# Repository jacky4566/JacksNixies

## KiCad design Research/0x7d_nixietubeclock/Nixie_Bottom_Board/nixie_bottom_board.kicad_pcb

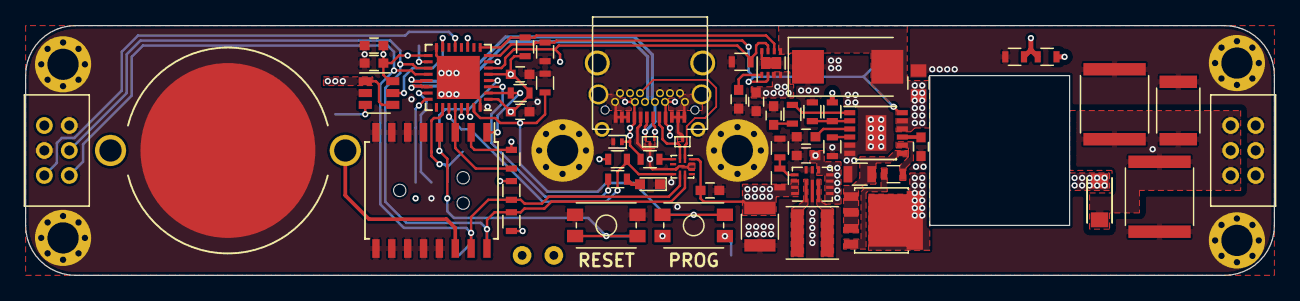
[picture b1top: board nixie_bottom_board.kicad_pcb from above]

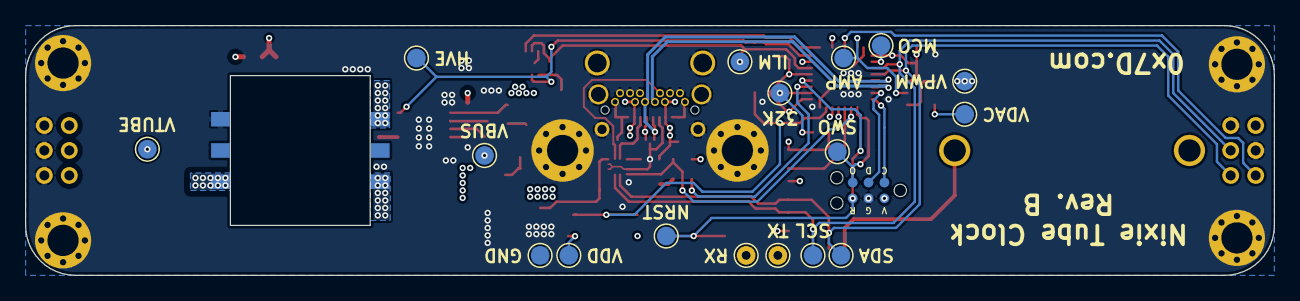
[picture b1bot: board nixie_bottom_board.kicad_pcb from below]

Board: 4 copper layers, 100.0 x 20.0 mm, 83 parts (18 on the bottom side), 49 nets.

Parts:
BT1: CR1620; CR1620_Holder_TH
C1: 330uF; CP_Tantalum_Case-X_EIA-7343-43_Reflow
C2, C12, C14, C15: 0.1uF; C_0603
C3: 10uF; C_0603
C4: C_IN; C_0805
C5: C_VC; C_0603
C6: C_SS; C_0603
C7: C_BP; C_0603
C8, C10: C_OUT; C_2220
C9: C_OUT; C_1812
C11: 220uF; C_1210
C13: 4.7uF; C_0603
C16: 1uF; C_0603
C17: SLEW; C_0603
D1: D_VBUS; X1SON
D2, D3: ESD122; DMX0003A
D4: D_RECT; SOD-123W
D5: LED; LED_0603
J1: USB_C_Receptacle; USB_C_Receptacle_Circular_Holes
J2: SWD; TC2030-MCP-NL
J3: Nixie_HV; Pin_Header_Harwin_2x03_Pitch2.00mm
J4: Nixie_CTRL; Pin_Header_Harwin_2x03_Pitch2.00mm
J5: MCO; TestPoint_Pad_D1.5mm
J6: ILM; TestPoint_Pad_D1.5mm
J7: HV_EN; TestPoint_Pad_D1.5mm
J8: HV_OUT; TestPoint_Pad_D1.5mm
J9: AMP_EN; TestPoint_Pad_D1.5mm
J10: 32kHz; TestPoint_Pad_D1.5mm
J11: SCL; TestPoint_Pad_D1.5mm
J12: SDA; TestPoint_Pad_D1.5mm
J13: DAC; TestPoint_Pad_D1.5mm
J14: VDD; TestPoint_Pad_D1.5mm
J15: VNIXIE; TestPoint_Pad_D1.5mm
J16: VBUS; TestPoint_Pad_D1.5mm
J17: SWO; TestPoint_Pad_D1.5mm
J18: NRST; TestPoint_Pad_D1.5mm
J19: TX; TestPoint_THTPad_D1.5mm_Drill0.7mm
J20: RX; TestPoint_THTPad_D1.5mm_Drill0.7mm
J21: GND; TestPoint_Pad_D1.5mm
L1: 1uH; Inductor_4.1x4.1mm
MH1, MH2, MH3, MH4, MH5, MH6: MountingHole_Pad; MountingHole_2.5mm_Pad_Via
Q1: Q_SWITCH; SOT-669_LFPAK
R1: 900k; R_0603
R2, R20: 1M; R_0603
R3, R12, R15, R19: 20k; R_0603
R4, R5, R13, R18: 10k; R_0603
R6: R_FREQ; R_0603
R7: R_VC; R_0603
R8: R_GATE; R_0603
R9: R_BIAS; R_0603
R10: R_FB; R_0603
R11: R_SENSE; R_0805
R14: 680; R_0603
R16: 560k; R_0603
R17: 180k; R_0603
R21: 15k; R_0603
SW1: NRST; EVQP2
SW2: DFU; EVQP2
T1: Wurth_Transformer_10.16x13.36mm; Wurth_WE-FB_10.18x13.36mm_Reverse
U1: TUSB322; X2QFN-12_1.6x1.6mm_Pitch0.4mm
U2: STM32L432K; QFN-32-1EP_5x5mm_Pitch0.5mm
U3: TPS63025X; VQFN-14_2.5x3mm_Pitch0.5mm
U4: DS3231; SOIC-16W_7.5x10.3mm_Pitch1.27mm
U5: AD8591; SOT-23-6
U6: LTC3759; MSOP-12-1EP_3x4mm_Pitch0.65mm
U7: TPS2595x0; WSON-8_1EP_2x2mm_Pitch0.5mm

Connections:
/32kHz: J10.1, R18.2, U2.2, U4.1
/AMP_EN: J9.1, U2.15, U5.5
/CC1: D2.2, J1.A5, U1.2
/CC2: D2.3, J1.B5, U1.1
/DAC: J13.1, U2.11, U5.3
/FAULT: R15.2, U2.9, U7.6
/GND: BT1.2, C1.1, C2.2, C3.2, C4.1, C5.2, C6.2, C7.2, C8.1, C9.1, C10.1, C11.1, C12.2, C13.2, C14.1, C15.1, C16.2, C17.2, D1.2, D2.1, D3.1, D5.1, J1.A1, J1.A2, J1.A3, J1.A8, J1.A10, J1.A11, J1.A12, J1.B1, J1.B2, J1.B3, J1.B8, J1.B10, J1.B11, J1.B12, J1.S1, J2.4, J3.2, J3.4, J3.6, J4.2, J4.3, J21.1, MH1.1, MH2.1, MH3.1, MH4.1, MH5.1, MH6.1, R2.2, R6.1, R9.1, R11.1, R12.2, R14.2, R17.1, R21.1, SW1.1, T1.1, U1.5, U1.10, U1.11, U2.16, U2.32, U2.33, U3.2, U3.9, U3.10, U4.5, U4.6, U4.7, U4.8, U4.9, U4.10, U4.11, U4.12, U4.13, U5.2, U6.5, U6.6, U6.13, U7.8, U7.9
/HV_EN: J7.1, R12.1, U2.8, U6.12, U7.2
/HV_IN: C1.2, C4.2, T1.6, U6.10, U6.11, U7.5
/HV_OUT: C8.2, C9.2, C10.2, D4.1, J3.1, J3.3, J3.5, J8.1, R10.1, R20.1
/ILM: J6.1, R14.1, U2.6, U7.7
/LED: R13.1, U2.3
/MCO: J5.1, U2.18
/NIXIE_EN: J4.5, U2.13
/NRST: J2.6, J18.1, SW1.2, U2.4, U4.4
/RTC: R19.1, U2.28, U4.3
/SCL: J4.4, J11.1, R5.1, U1.8, U2.19, U4.16
/SDA: J4.6, J12.1, R4.1, U1.7, U2.20, U4.15
/SWCLK: J2.1, U2.24
/SWDIO: J2.3, U2.23
/SWO: J2.5, J17.1, U2.26
/UART_RX: J20.1, U2.30
/UART_TX: J19.1, U2.29
/USB: R3.2, U1.6, U2.27
/USB_N: D3.3, J1.A7, J1.B7, U2.21
/USB_P: D3.2, J1.A6, J1.B6, U2.22
/VBUS: C2.1, C3.1, D1.1, J1.A4, J1.A9, J1.B4, J1.B9, J16.1, R1.1, U3.4, U3.5, U3.6, U3.7, U3.8, U7.3, U7.4
/VDD: C11.2, C12.1, C13.1, C14.2, C15.2, C16.1, J2.2, J14.1, R3.1, R4.2, R5.2, R15.1, R16.2, R18.1, R19.2, SW2.2, U1.12, U2.1, U2.5, U2.17, U3.12, U3.13, U3.14, U4.2, U5.6
/VNIXIE: J4.1, J15.1, U5.1, U5.4
unnamed: BT1.1, U4.14
unnamed: C5.1, R7.2
unnamed: C6.1, U6.3
unnamed: C7.1, U6.9
unnamed: C17.1, U7.1
unnamed: D4.2, T1.3
unnamed: D5.2, R13.2
unnamed: L1.1, U3.3
unnamed: L1.2, U3.1
unnamed: Q1.1, T1.4
unnamed: Q1.2, R8.1
unnamed: Q1.3, R11.2, U6.7
unnamed: R1.2, U1.3
unnamed: R2.1, SW2.1, U2.31
unnamed: R6.2, U6.4
unnamed: R7.1, U6.1
unnamed: R8.2, U6.8
unnamed: R9.2, R10.2, U6.2
unnamed: R16.1, R17.2, U3.11
unnamed: R20.2, R21.2, U2.7

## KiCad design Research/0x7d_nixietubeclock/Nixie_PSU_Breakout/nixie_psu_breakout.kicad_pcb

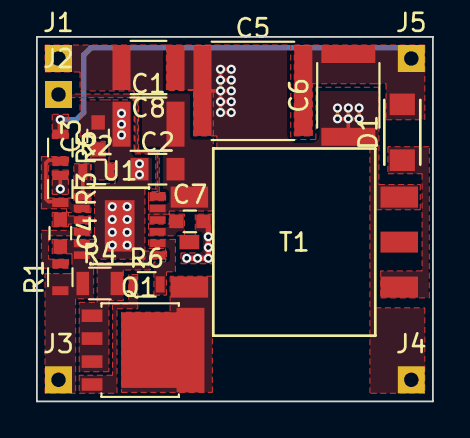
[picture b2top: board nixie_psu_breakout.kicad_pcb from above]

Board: 2 copper layers, 22.0 x 20.2 mm, 23 parts (0 on the bottom side), 15 nets.

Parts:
C1, C8: C_IN; C_1210
C2: C_IN; C_0805
C3: C_VC; C_0603
C4: C_SS; C_0603
C5: C_OUT; C_2220
C6: C_OUT; C_1812
C7: C_BP; C_0603
D1: D_RECT; SOD-123W
J1: VIN; Measurement_Point_Square-TH_Small
J2: EN; Measurement_Point_Square-TH_Small
J3, J4: GND; Measurement_Point_Square-TH_Small
J5: VOUT; Measurement_Point_Square-TH_Small
Q1: Q_SWITCH; SOT-669_LFPAK
R1: R_FREQ; R_0603
R2: R_VC; R_0603
R3: R_BIAS; R_0603
R4: R_SENSE; R_0805
R5: R_FB; R_0603
R6: R_GATE; R_0603
T1: Wurth_Transformer_10.16x13.36mm; Wurth_WE-FB_10.18x13.36mm
U1: LTC3759; MSOP-12-1EP_3x4mm_Pitch0.65mm

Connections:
GNDREF: C1.1, C2.1, C3.2, C4.2, C5.1, C6.1, C7.2, C8.1, J3.1, J4.1, R1.1, R3.1, R4.1, T1.1, U1.5, U1.6, U1.13
unnamed: C1.2, C2.2, C8.2, J1.1, T1.6, U1.10, U1.11
unnamed: C3.1, R2.2
unnamed: C4.1, U1.3
unnamed: C5.2, C6.2, D1.1, J5.1, R5.1
unnamed: C7.1, U1.9
unnamed: D1.2, T1.3
unnamed: J2.1, U1.12
unnamed: Q1.1, T1.4
unnamed: Q1.2, R6.1
unnamed: Q1.3, R4.2, U1.7
unnamed: R1.2, U1.4
unnamed: R2.1, U1.1
unnamed: R3.2, R5.2, U1.2
unnamed: R6.2, U1.8

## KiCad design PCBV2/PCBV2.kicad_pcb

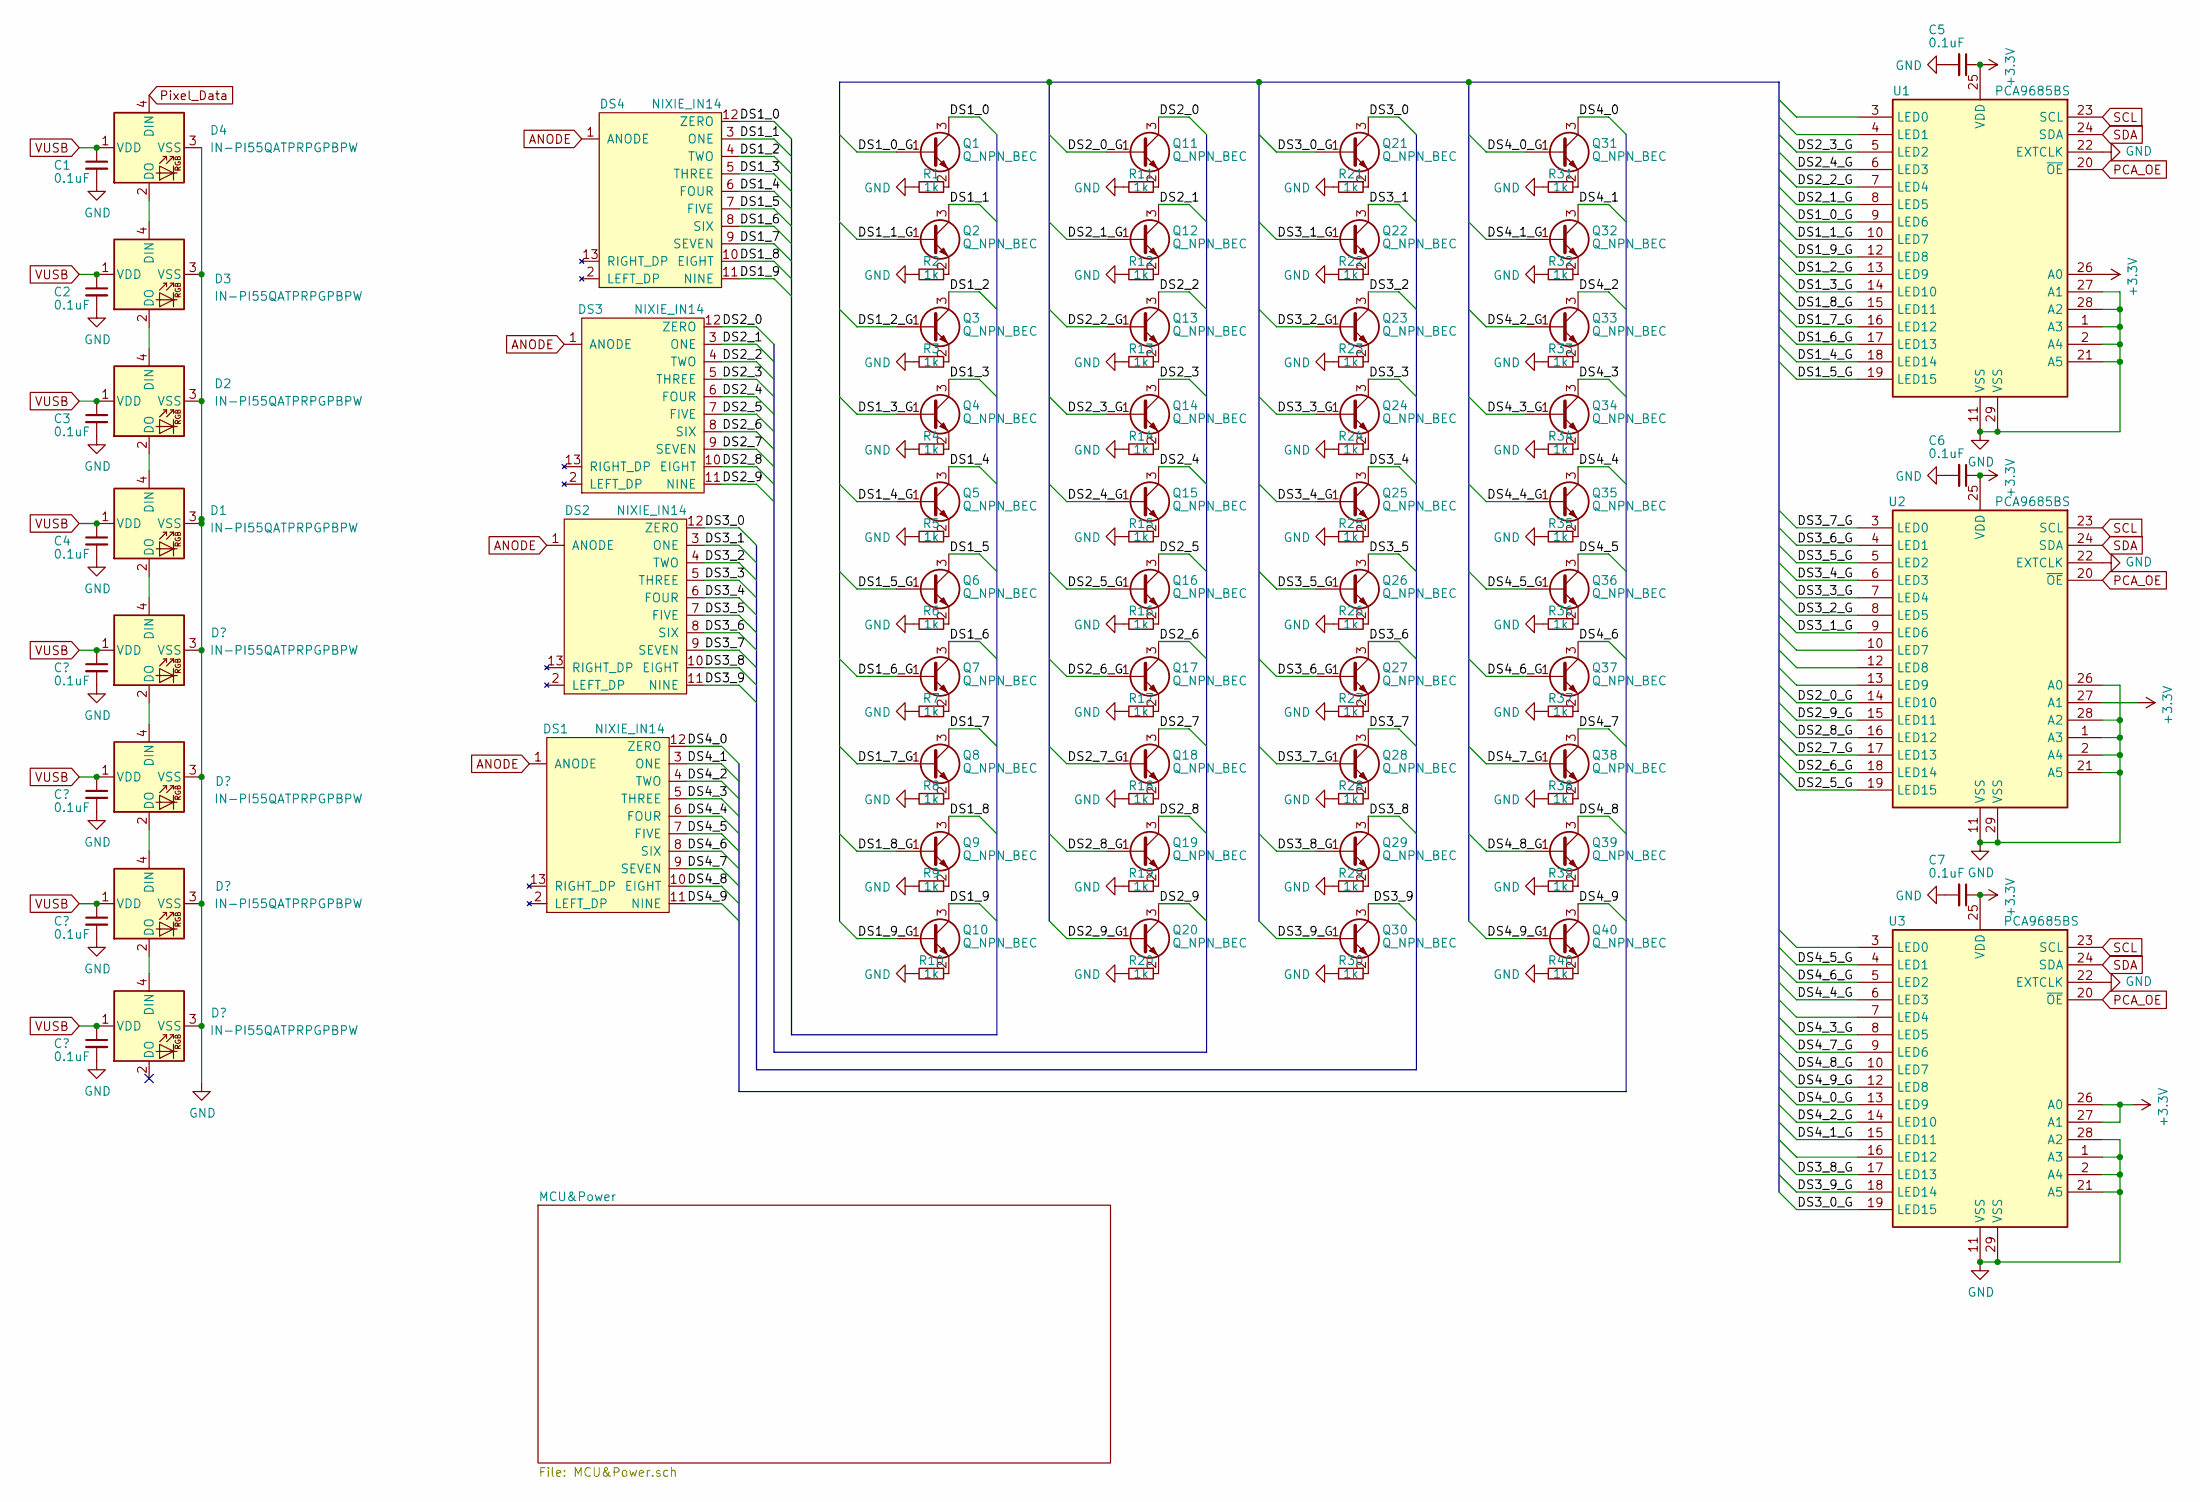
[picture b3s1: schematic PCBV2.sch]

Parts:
C1, C2, C3, C4, C5, C6, C7: 0.1uF; C_0603_1608Metric
D1, D2, D3, D4: IN-PI55QATPRPGPBPW; LED_Inolux_IN-PI554FCH_PLCC4_5.0x5.0mm_P3.2mm
DS1, DS2, DS3, DS4: NIXIE_IN14; Nixie_IN_14
Q1, Q2, Q3, Q4, Q5, Q6, Q7, Q8, Q9, Q10, Q11, Q12, Q13, Q14, Q15, Q16, Q17, Q18, Q19, Q20, Q21, Q22, Q23, Q24, Q25, Q26, Q27, Q28, Q29, Q30, Q31, Q32, Q33, Q34, Q35, Q36, Q37, Q38, Q39, Q40: Q_NPN_BEC; SOT-323; Manufacturer Part Number MSD42WT1G
R1, R2, R3, R4, R5, R6, R7, R8, R9, R10, R11, R12, R13, R14, R15, R16, R17, R18, R19, R20, R21, R22, R23, R24, R25, R26, R27, R28, R29, R30, R31, R32, R33, R34, R35, R36, R37, R38, R39, R40: 1k; R_0603_1608Metric
U1, U2, U3: PCA9685BS; QFN-28-1EP_6x6mm_P0.65mm_EP4.25x4.25mm_ThermalVias

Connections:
+3V3: C5.1, C6.1, C7.1, U1.25 (VDD), U1.26 (A0), U2.25 (VDD), U2.27 (A1), U3.25 (VDD), U3.26 (A0), U3.27 (A1); also elsewhere on the board
/DS1_0: DS4.12 (ZERO), Q1.3 (C)
/DS1_0_G: Q1.1 (B), U1.9 (LED6)
/DS1_1: DS4.3 (ONE), Q2.3 (C)
/DS1_1_G: Q2.1 (B), U1.10 (LED7)
/DS1_2: DS4.4 (TWO), Q3.3 (C)
/DS1_2_G: Q3.1 (B), U1.13 (LED9)
/DS1_3: DS4.5 (THREE), Q4.3 (C)
/DS1_3_G: Q4.1 (B), U1.14 (LED10)
/DS1_4: DS4.6 (FOUR), Q5.3 (C)
/DS1_4_G: Q5.1 (B), U1.18 (LED14)
/DS1_5: DS4.7 (FIVE), Q6.3 (C)
/DS1_5_G: Q6.1 (B), U1.19 (LED15)
/DS1_6: DS4.8 (SIX), Q7.3 (C)
/DS1_6_G: Q7.1 (B), U1.17 (LED13)
/DS1_7: DS4.9 (SEVEN), Q8.3 (C)
/DS1_7_G: Q8.1 (B), U1.16 (LED12)
/DS1_8: DS4.10 (EIGHT), Q9.3 (C)
/DS1_8_G: Q9.1 (B), U1.15 (LED11)
/DS1_9: DS4.11 (NINE), Q10.3 (C)
/DS1_9_G: Q10.1 (B), U1.12 (LED8)
/DS2_0: DS3.12 (ZERO), Q11.3 (C)
/DS2_0_G: Q11.1 (B), U2.14 (LED10)
/DS2_1: DS3.3 (ONE), Q12.3 (C)
/DS2_1_G: Q12.1 (B), U1.8 (LED5)
/DS2_2: DS3.4 (TWO), Q13.3 (C)
/DS2_2_G: Q13.1 (B), U1.7 (LED4)
/DS2_3: DS3.5 (THREE), Q14.3 (C)
/DS2_3_G: Q14.1 (B), U1.5 (LED2)
/DS2_4: DS3.6 (FOUR), Q15.3 (C)
/DS2_4_G: Q15.1 (B), U1.6 (LED3)
/DS2_5: DS3.7 (FIVE), Q16.3 (C)
/DS2_5_G: Q16.1 (B), U2.19 (LED15)
/DS2_6: DS3.8 (SIX), Q17.3 (C)
/DS2_6_G: Q17.1 (B), U2.18 (LED14)
/DS2_7: DS3.9 (SEVEN), Q18.3 (C)
/DS2_7_G: Q18.1 (B), U2.17 (LED13)
/DS2_8: DS3.10 (EIGHT), Q19.3 (C)
/DS2_8_G: Q19.1 (B), U2.16 (LED12)
/DS2_9: DS3.11 (NINE), Q20.3 (C)
/DS2_9_G: Q20.1 (B), U2.15 (LED11)
/DS3_0: DS2.12 (ZERO), Q21.3 (C)
/DS3_0_G: Q21.1 (B), U3.19 (LED15)
/DS3_1: DS2.3 (ONE), Q22.3 (C)
/DS3_1_G: Q22.1 (B), U2.9 (LED6)
/DS3_2: DS2.4 (TWO), Q23.3 (C)
/DS3_2_G: Q23.1 (B), U2.8 (LED5)
/DS3_3: DS2.5 (THREE), Q24.3 (C)
/DS3_3_G: Q24.1 (B), U2.7 (LED4)
/DS3_4: DS2.6 (FOUR), Q25.3 (C)
/DS3_4_G: Q25.1 (B), U2.6 (LED3)
/DS3_5: DS2.7 (FIVE), Q26.3 (C)
/DS3_5_G: Q26.1 (B), U2.5 (LED2)
/DS3_6: DS2.8 (SIX), Q27.3 (C)
/DS3_6_G: Q27.1 (B), U2.4 (LED1)
/DS3_7: DS2.9 (SEVEN), Q28.3 (C)
/DS3_7_G: Q28.1 (B), U2.3 (LED0)
/DS3_8: DS2.10 (EIGHT), Q29.3 (C)
/DS3_8_G: Q29.1 (B), U3.17 (LED13)
/DS3_9: DS2.11 (NINE), Q30.3 (C)
/DS3_9_G: Q30.1 (B), U3.18 (LED14)
/DS4_0: DS1.12 (ZERO), Q31.3 (C)
/DS4_0_G: Q31.1 (B), U3.13 (LED9)
/DS4_1: DS1.3 (ONE), Q32.3 (C)
/DS4_1_G: Q32.1 (B), U3.15 (LED11)
/DS4_2: DS1.4 (TWO), Q33.3 (C)
/DS4_2_G: Q33.1 (B), U3.14 (LED10)
/DS4_3: DS1.5 (THREE), Q34.3 (C)
/DS4_3_G: Q34.1 (B), U3.8 (LED5)
/DS4_4: DS1.6 (FOUR), Q35.3 (C)
/DS4_4_G: Q35.1 (B), U3.6 (LED3)
/DS4_5: DS1.7 (FIVE), Q36.3 (C)
/DS4_5_G: Q36.1 (B), U3.4 (LED1)
/DS4_6: DS1.8 (SIX), Q37.3 (C)
/DS4_6_G: Q37.1 (B), U3.5 (LED2)
/DS4_7: DS1.9 (SEVEN), Q38.3 (C)
/DS4_7_G: Q38.1 (B), U3.9 (LED6)
/DS4_8: DS1.10 (EIGHT), Q39.3 (C)
/DS4_8_G: Q39.1 (B), U3.10 (LED7)
/DS4_9: DS1.11 (NINE), Q40.3 (C)
/DS4_9_G: Q40.1 (B), U3.12 (LED8)
ANODE: DS1.1 (ANODE), DS2.1 (ANODE), DS3.1 (ANODE), DS4.1 (ANODE); also elsewhere on the board
GND: C1.2, C2.2, C3.2, C4.2, C5.2, C6.2, C7.2, D1.3 (VSS), D2.3 (VSS), D3.3 (VSS), D4.3 (VSS), R1.2, R2.2, R3.2, R4.2, R5.2, R6.2, R7.2, R8.2, R9.2, R10.2, R11.2, R12.2, R13.2, R14.2, R15.2, R16.2, R17.2, R18.2, R19.2, R20.2, R21.2, R22.2, R23.2, R24.2, R25.2, R26.2, R27.2, R28.2, R29.2, R30.2, R31.2, R32.2, R33.2, R34.2, R35.2, R36.2, R37.2, R38.2, R39.2, R40.2, U1.1 (A3), U1.2 (A4), U1.11 (VSS), U1.21 (A5), U1.22 (EXTCLK), U1.27 (A1), U1.28 (A2), U1.29 (VSS), U2.1 (A3), U2.2 (A4), U2.11 (VSS), U2.21 (A5), U2.22 (EXTCLK), U2.26 (A0), U2.28 (A2), U2.29 (VSS), U3.1 (A3), U3.2 (A4), U3.11 (VSS), U3.21 (A5), U3.22 (EXTCLK), U3.28 (A2), U3.29 (VSS); also elsewhere on the board
unnamed: D1.4 (DIN), D2.2 (DO)
unnamed: D2.4 (DIN), D3.2 (DO)
unnamed: D3.4 (DIN), D4.2 (DO)
unnamed: Q1.2 (E), R1.1
unnamed: Q2.2 (E), R2.1
unnamed: Q3.2 (E), R3.1
unnamed: Q4.2 (E), R4.1
unnamed: Q5.2 (E), R5.1
unnamed: Q6.2 (E), R6.1
unnamed: Q7.2 (E), R7.1
unnamed: Q8.2 (E), R8.1
unnamed: Q9.2 (E), R9.1
unnamed: Q10.2 (E), R10.1
unnamed: Q11.2 (E), R11.1
unnamed: Q12.2 (E), R12.1
unnamed: Q13.2 (E), R13.1
unnamed: Q14.2 (E), R14.1
unnamed: Q15.2 (E), R15.1
unnamed: Q16.2 (E), R16.1
unnamed: Q17.2 (E), R17.1
unnamed: Q18.2 (E), R18.1
unnamed: Q19.2 (E), R19.1
unnamed: Q20.2 (E), R20.1
unnamed: Q21.2 (E), R21.1
unnamed: Q22.2 (E), R22.1
unnamed: Q23.2 (E), R23.1
unnamed: Q24.2 (E), R24.1
unnamed: Q25.2 (E), R25.1
unnamed: Q26.2 (E), R26.1
unnamed: Q27.2 (E), R27.1
unnamed: Q28.2 (E), R28.1
unnamed: Q29.2 (E), R29.1
unnamed: Q30.2 (E), R30.1
unnamed: Q31.2 (E), R31.1
unnamed: Q32.2 (E), R32.1
unnamed: Q33.2 (E), R33.1
unnamed: Q34.2 (E), R34.1
unnamed: Q35.2 (E), R35.1
unnamed: Q36.2 (E), R36.1
unnamed: Q37.2 (E), R37.1
unnamed: Q38.2 (E), R38.1
unnamed: Q39.2 (E), R39.1
unnamed: Q40.2 (E), R40.1
PCA_OE: U1.20 (~OE), U2.20 (~OE), U3.20 (~OE); also elsewhere on the board
Pixel_Data: D4.4 (DIN); also elsewhere on the board
SCL: U1.23 (SCL), U2.23 (SCL), U3.23 (SCL); also elsewhere on the board
SDA: U1.24 (SDA), U2.24 (SDA), U3.24 (SDA); also elsewhere on the board
VUSB: C1.1, C2.1, C3.1, C4.1, D1.1 (VDD), D2.1 (VDD), D3.1 (VDD), D4.1 (VDD); also elsewhere on the board

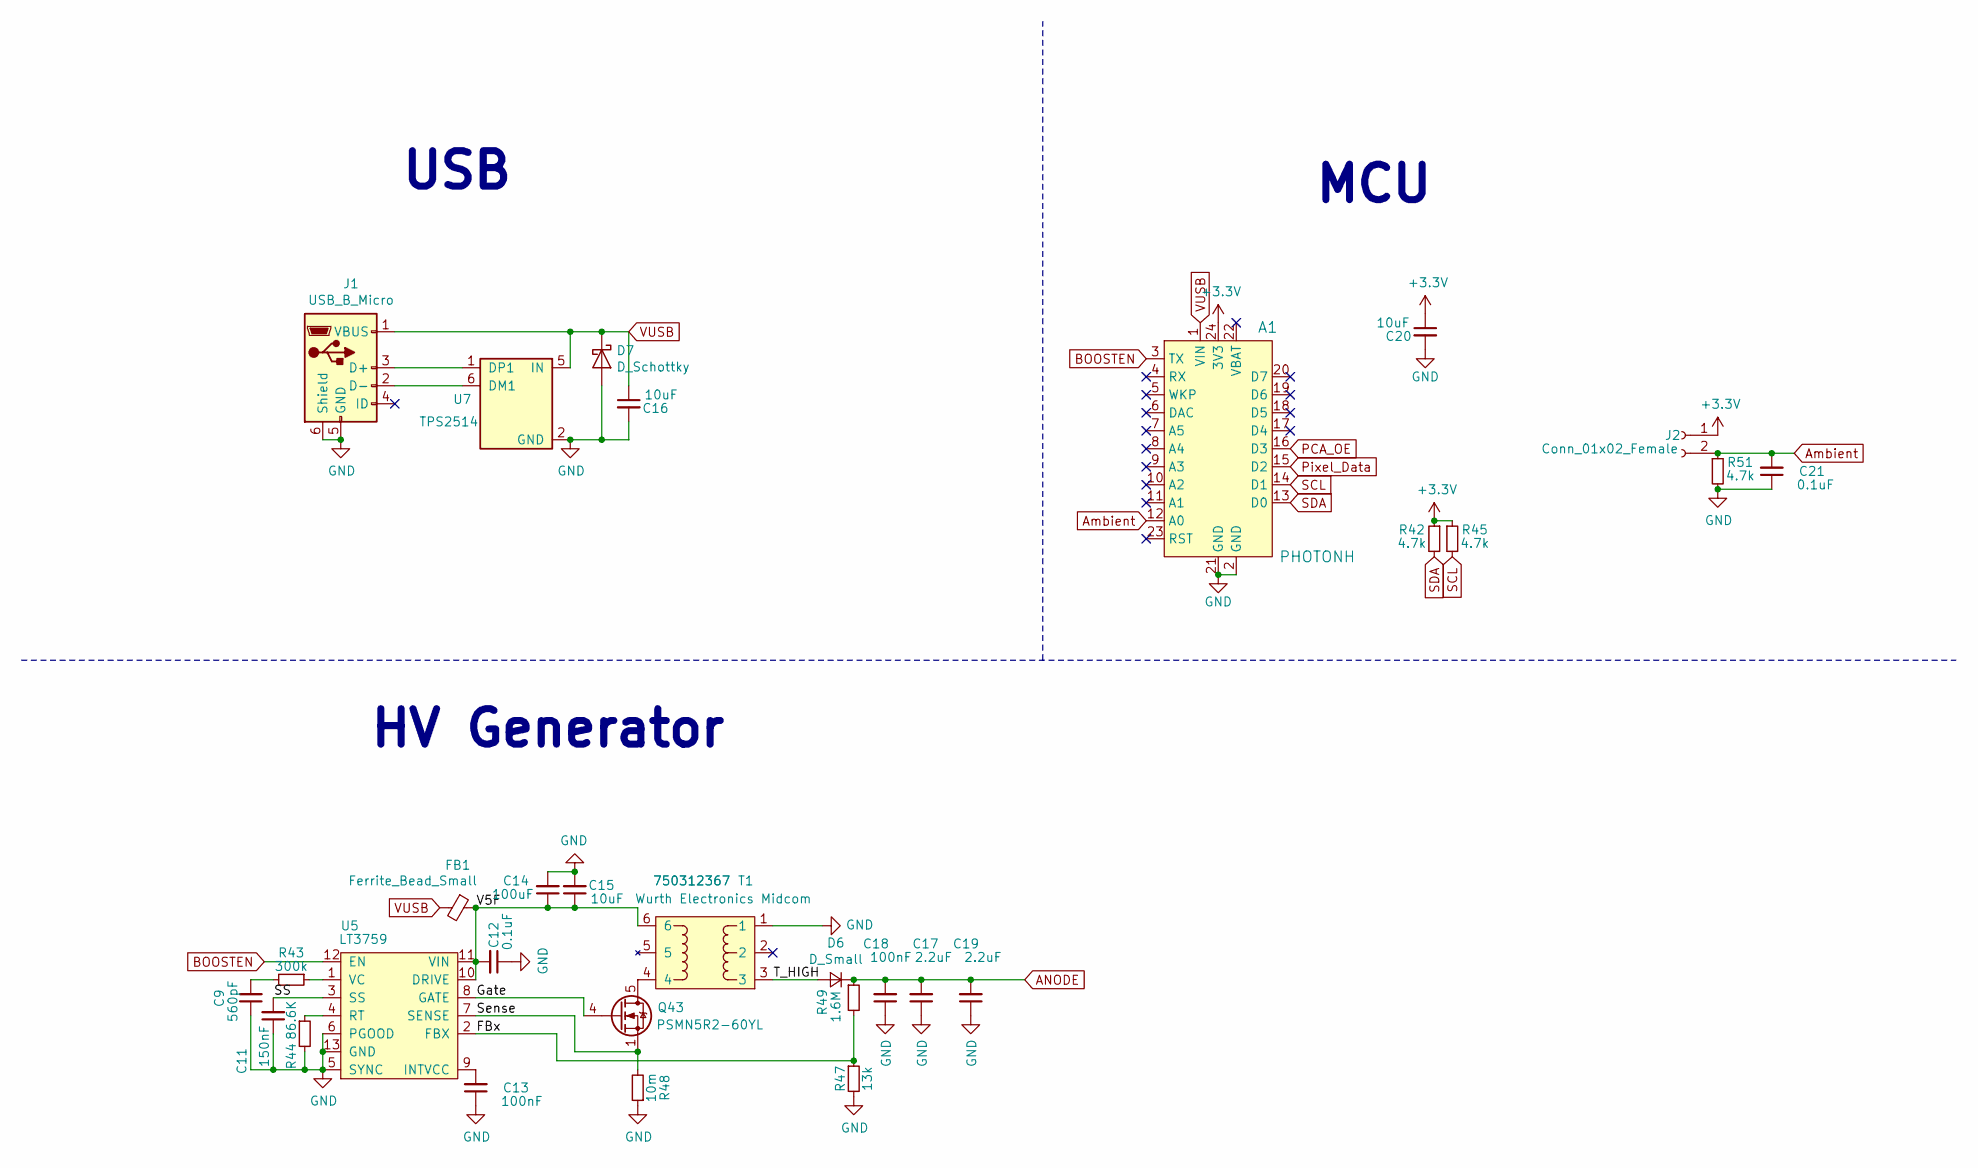
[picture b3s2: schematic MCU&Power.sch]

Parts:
A1: PHOTONH; Particle_Photon; MPN PHOTONH; Digi-Key_PN 1878-1000-ND
C9: 560pF; C_0603_1608Metric
C11: 150nF; C_0603_1608Metric
C12, C21: 0.1uF; C_0603_1608Metric
C13: 100nF; C_0603_1608Metric
C14: 100uF; C_1206_3216Metric
C15, C16, C20: 10uF; C_0805_2012Metric
C17, C19: 2.2uF; C_2220_5650Metric
C18: 100nF; C_1210_3225Metric
D6: D_Small; D_SOD-123; Part UF1GLWHRVGCT-ND
D7: D_Schottky; D_SOD-123
FB1: Ferrite_Bead_Small; R_0805_2012Metric
J1: USB_B_Micro; USB_Micro-B_GCT_USB3076-30-A
J2: Conn_01x02_Female; PinHeader_1x02_P2.54mm_Vertical
Q43: PSMN5R2-60YL; LFPAK56
R42, R45, R51: 4.7k; R_0603_1608Metric
R43: 300k; R_0603_1608Metric
R44: 86.6K; R_0603_1608Metric
R47: 13k; R_0603_1608Metric
R48: 10m; R_1206_3216Metric
R49: 1.6M; R_0603_1608Metric
T1: 750312367; Manufacturer Part Number 750312367
U5: LT3759; MSOP-12-1EP_3x4mm_P0.65mm_EP1.65x2.85mm_ThermalVias
U7: TPS2514; SOT-23-6

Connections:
+3V3: A1.24 (3V3), C20.1, J2.1, R42.1, R45.1; also elsewhere on the board
/MCU&Power/FBx: R47.1, R49.2, U5.2 (FBX)
/MCU&Power/Gate: Q43.4 (G), U5.8 (GATE)
/MCU&Power/SPI_CLK: A1.9 (A3); also elsewhere on the board
/MCU&Power/SPI_CS: A1.10 (A2); also elsewhere on the board
/MCU&Power/SPI_MISO: A1.8 (A4); also elsewhere on the board
/MCU&Power/SPI_MOSI: A1.7 (A5); also elsewhere on the board
/MCU&Power/SS: C11.2, U5.3 (SS)
/MCU&Power/Sense: Q43.1 (S), Q43.2 (S), Q43.3 (S), R48.2, U5.7 (SENSE)
/MCU&Power/T_HIGH: D6.2 (A), T1.3
/MCU&Power/V5F: C12.2, C14.1, C15.1, FB1.1, T1.6, U5.10 (DRIVE), U5.11 (VIN)
ANODE: C17.2, C18.2, C19.2, D6.1 (K), R49.1; also elsewhere on the board
Ambient: A1.12 (A0), C21.2, J2.2, R51.1
BOOSTEN: A1.3 (TX), U5.12 (EN)
GND: A1.2 (GND), A1.21 (GND), C9.1, C11.1, C12.1, C13.1, C14.2, C15.2, C16.2, C17.1, C18.1, C19.1, C20.2, C21.1, D7.2 (A), J1.5 (GND), J1.6 (Shield), R44.2, R47.2, R48.1, R51.2, T1.1, U5.5 (SYNC), U5.6 (PGOOD), U5.13 (GND), U7.2 (GND); also elsewhere on the board
MOTION: A1.17 (D4); also elsewhere on the board
unnamed: C9.2, R43.2
unnamed: C13.2, U5.9 (INTVCC)
unnamed: J1.2 (D-), U7.6 (DM1)
unnamed: J1.3 (D+), U7.1 (DP1)
unnamed: Q43.5 (D), T1.4
unnamed: R43.1, U5.1 (VC)
unnamed: R44.1, U5.4 (RT)
PCA_OE: A1.16 (D3); also elsewhere on the board
Pixel_Data: A1.15 (D2); also elsewhere on the board
SCL: A1.14 (D1), R45.2; also elsewhere on the board
SDA: A1.13 (D0), R42.2; also elsewhere on the board
SenseHigh: A1.20 (D7); also elsewhere on the board
VUSB: A1.1 (VIN), C16.1, D7.1 (K), FB1.2, J1.1 (VBUS), U7.5 (IN); also elsewhere on the board

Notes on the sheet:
USB
HV Generator
MCU

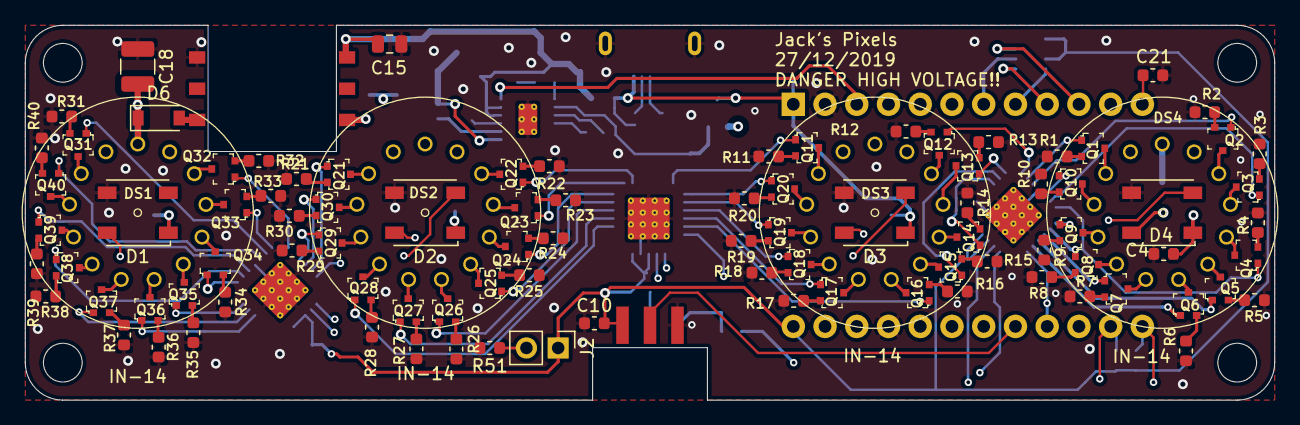
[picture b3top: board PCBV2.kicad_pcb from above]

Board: 4 copper layers, 100.0 x 30.0 mm, 135 parts (0 on the bottom side), 154 nets.

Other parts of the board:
C8, C10: 0.1uF; C_0603_1608Metric
R41, R50: 1M; R_0603_1608Metric
R46: 86.6k; R_0603_1608Metric
U6: BME680; Bosch_LGA-8_3x3mm_P0.8mm_ClockwisePinNumbering
U8: AM612; AM612_Horz

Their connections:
+3V3: C8.1, C10.2, R50.2, U6.6, U6.8, U8.4; also elsewhere on the board
/MCU&Power/SPI_CLK: U6.4; also elsewhere on the board
/MCU&Power/SPI_CS: U6.2; also elsewhere on the board
/MCU&Power/SPI_MISO: U6.5; also elsewhere on the board
/MCU&Power/SPI_MOSI: U6.3; also elsewhere on the board
GND: C8.2, C10.1, R46.2, U6.1, U6.7, U8.3, U8.6; also elsewhere on the board
MOTION: U8.5; also elsewhere on the board
unnamed: R41.2, R46.1, U8.1
unnamed: R50.1, U8.2
SenseHigh: R41.1; also elsewhere on the board

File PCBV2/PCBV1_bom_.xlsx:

Component | Description | Part | References | Value | Footprint | Quantity Per PCB | Digikey Part Num
1 | PHOTON WITH HEADERS | PHOTONH | A1 | PHOTONH | Particle_Photon | 1 | 1878-1005-ND
2 | Unpolarized capacitor, small symbol | C_Small | C1 C2 C3 C4 C5 C6 C7 C8 C10 C12 C13 C21 | 0.1uF | C_0603_1608Metric | 12 | 1276-1000-1-ND
3 | Unpolarized capacitor, small symbol | C_Small | C14 | 100uF | C_1206_3216Metric | 1 | 1276-1782-1-ND
4 | Unpolarized capacitor, small symbol | C_Small | C15 C16 C20 | 10uF | C_0805_2012Metric | 2 | 1276-2893-1-ND
5 | Unpolarized capacitor, small symbol | C_Small | C11 | 150nF | C_0603_1608Metric | 1 | 1276-1972-1-ND
6 | Unpolarized capacitor, small symbol | C_Small | C17 C18 C19 | 2.2uF | C_1210_3225Metric | 3 | 587-3380-1-ND
9 | Unpolarized capacitor, small symbol | C_Small | C9 | 560pF | C_0603_1608Metric | 1 | 490-1468-1-ND
10 | Bidirectional transient-voltage-suppression diode | D_TVS | D5 | 5.6V | D_SMA | 1 | SMAJ5.0ALFTR-ND
11 | Schottky diode | D_Schottky | D7, D6 | D_Schottky | D_SOD-123 | 2 | UF1GLWHRVGCT-ND
13 | 5050 RGBW LED 4-Pin with integrated IC | IN-PI55QATPRPGPBPW | D1 D2 D3 D4 | IN-PI55QATPRPGPBPW | LED_Inolux_IN-PI554FCH_PLCC4_5.0x5.0mm_P3.2mm | 4 | 1830-1210-2-ND
14 |  | NIXIE_IN14 | DS1 DS2 DS3 DS4 | NIXIE_IN14 | Nixie_IN_14 | 4
15 | Ferrite bead, small symbol | Ferrite_Bead_Small | FB1 | Ferrite_Bead_Small | R_0805_2012Metric | 1 | 732-1620-1-ND
16 | Generic connector, single row, 01x02, script generated (kicad-library-utils/sch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 | Conn_01x02_Female | J2 | Conn_01x02_Female | PinHeader_1x02_P2.54mm_Vertical | 1 | 475-1077-ND
17 | USB Micro Type B connector | USB_B_Micro | J1 | USB_B_Micro | USB_Micro-B_GCT_USB3076-30-A | 1 | 2073-USB3076-30-ACT-ND
18 | 100A, 60V Vds, N-Channel MOSFET, 5.2mOhm Ron, LFPAK56 | PSMN5R2-60YL | Q43 | PSMN5R2-60YL | LFPAK56 | 1 | 1727-2595-1-ND
19 | NPN transistor, base/emitter/collector | Q_NPN_BEC | Q1 Q2 Q3 Q4 Q5 Q6 Q7 Q8 Q9 Q10 Q11 Q12 Q13 Q14 Q15 Q16 Q17 Q18 Q19 Q20 Q21 Q22 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 | Q_NPN_BEC | SOT-323 | 40 | MSD42WT1GOSCT-ND
20 | Resistor, small symbol | R_Small | R49 | 1.6M | R_0603_1608Metric | 1 | P1.60MHCT-ND
21 | Resistor, small symbol | R_Small | R48 | 10m | R_1206_3216Metric | 1 | ERJ-8CWFR010V
22 | Resistor, small symbol | R_Small | R47 | 13k | R_0603_1608Metric | 1 | P13.0KHCT-ND
23 | Resistor, small symbol | R_Small | R41 R50 | 1M | R_0603_1608Metric | 2 | P1.00MHCT-ND
24 | Resistor, small symbol | R_Small | R1 R2 R3 R4 R5 R6 R7 R8 R9 R10 R11 R12 R13 R14 R15 R16 R17 R18 R19 R20 R21 R22 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 | 1k | R_0603_1608Metric | 40 | P1.00KHCT-ND
25 | Resistor, small symbol | R_Small | R43 | 300k | R_0603_1608Metric | 1 | P300KHCT-ND
26 | Resistor, small symbol | R_Small | R42 R45 R51 | 4.7k | R_0603_1608Metric | 3 | P4.70KHCT-ND
27 | Resistor, small symbol | R_Small | R44 R46 | 86.6K | R_0603_1608Metric | 2 | P86.6KHCT-ND
28 |  | 750312367 | T1 | 750312367 | 750312367 | 1 | 1297-1017-1-ND
29 |  | AM612-MargoGeneral | U8 | AM612 | AM612_Horz | 1
30 | It is a digital 4 in 1 sensor with gas, humidity, pressure and temperature meas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 | BME680 | U6 | BME680 | Bosch_LGA-8_3x3mm_P0.8mm_ClockwisePinNumbering | 1 | 828-1077-1-ND
31 |  | LT3759 | U5 | LT3759 | MSOP-12-1EP_3x4mm_P0.65mm_EP1.65x2.85mm_ThermalVias | 1 | LT3759EMSE#TRPBFCT-ND
32 | 16-channel 12-bit PWM Fm+ I2C-bus LED controller RGBA QFN | PCA9685BS | U1 U2 U3 | PCA9685BS | QFN-28-1EP_6x6mm_P0.65mm_EP4.25x4.25mm_ThermalVias | 3 | 568-5305-1-ND
33 | Single-Bit Dual-Supply Bus Transceiver With Configurable Voltage Translation an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 | SN74LVC1T45DRL | U4 | SN74LVC1T45DRL | SOT-563 | 1 | 296-20629-1-ND
34 | USB Dedicated Charging Port Controller | TPS2514 | U7 | TPS2514 | SOT-23-6 | 1 | 296-40725-1-ND

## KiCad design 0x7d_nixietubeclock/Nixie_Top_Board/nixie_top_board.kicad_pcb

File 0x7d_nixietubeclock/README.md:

# NixieTubeClock

Project files related to the Nixie Tube Clock project.

### Driver PCB

### Controller PCB

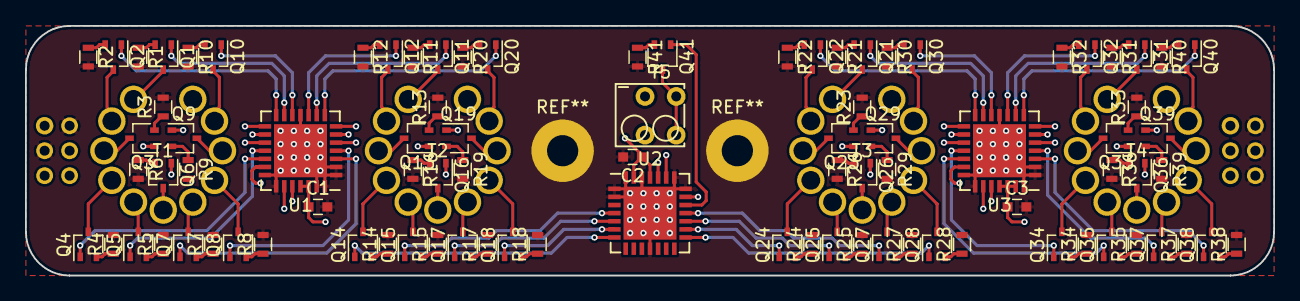
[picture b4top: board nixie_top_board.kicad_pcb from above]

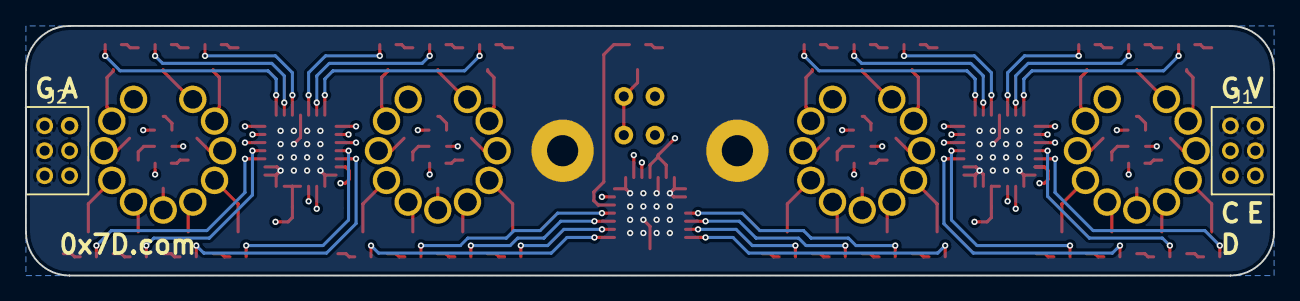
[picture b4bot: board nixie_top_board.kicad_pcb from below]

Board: 4 copper layers, 100.0 x 20.0 mm, 95 parts (2 on the bottom side), 129 nets.

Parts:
C1, C2, C3: Bypass; C_0603
J1, J2: Conn_02x03_Odd_Even; Pin_Header_Straight_2x03_Pitch2.00mm
Q1, Q2, Q3, Q4, Q5, Q6, Q7, Q8, Q9, Q10, Q11, Q12, Q13, Q14, Q15, Q16, Q17, Q18, Q19, Q20, Q21, Q22, Q23, Q24, Q25, Q26, Q27, Q28, Q29, Q30, Q31, Q32, Q33, Q34, Q35, Q36, Q37, Q38, Q39, Q40, Q41: Q_NPN_BEC; SOT-323_SC-70
R1, R2, R3, R4, R5, R6, R7, R8, R9, R10, R11, R12, R13, R14, R15, R16, R17, R18, R19, R20, R21, R22, R23, R24, R25, R26, R27, R28, R29, R30, R31, R32, R33, R34, R35, R36, R37, R38, R39, R40, R41: R; R_0603
T1, T2, T3, T4: IN-8
T5: IN-3; Phoenix_1770953
U1, U2, U3: PCA9685; QFN-28-1EP_6x6mm_Pitch0.65mm

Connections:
/ANODE: J2.1, J2.3, J2.5, T1.11, T2.11, T3.11, T4.11, T5.1
/GND: C1.2, C2.2, C3.2, J1.2, J1.3, J2.2, J2.4, J2.6, R1.2, R2.2, R3.2, R4.2, R5.2, R6.2, R7.2, R8.2, R9.2, R10.2, R11.2, R12.2, R13.2, R14.2, R15.2, R16.2, R17.2, R18.2, R19.2, R20.2, R21.2, R22.2, R23.2, R24.2, R25.2, R26.2, R27.2, R28.2, R29.2, R30.2, R31.2, R32.2, R33.2, R34.2, R35.2, R36.2, R37.2, R38.2, R39.2, R40.2, R41.2, U1.1, U1.2, U1.11, U1.21, U1.22, U1.27, U1.28, U1.29, U2.1, U2.2, U2.11, U2.21, U2.22, U2.26, U2.28, U2.29, U3.1, U3.2, U3.11, U3.21, U3.22, U3.28, U3.29
/SCL: J1.4, U1.23, U2.23, U3.23
/SDA: J1.6, U1.24, U2.24, U3.24
/T1_C_0: Q1.3, T1.1
/T1_C_1: Q2.3, T1.2
/T1_C_2: Q3.3, T1.3
/T1_C_3: Q4.3, T1.4
/T1_C_4: Q5.3, T1.5
/T1_C_5: Q6.3, T1.6
/T1_C_6: Q7.3, T1.7
/T1_C_7: Q8.3, T1.8
/T1_C_8: Q9.3, T1.9
/T1_C_9: Q10.3, T1.10
/T1_E_0: Q1.2, R1.1
/T1_E_1: Q2.2, R2.1
/T1_E_2: Q3.2, R3.1
/T1_E_3: Q4.2, R4.1
/T1_E_4: Q5.2, R5.1
/T1_E_5: Q6.2, R6.1
/T1_E_6: Q7.2, R7.1
/T1_E_7: Q8.2, R8.1
/T1_E_8: Q9.2, R9.1
/T1_E_9: Q10.2, R10.1
/T1_G_0: Q1.1, U1.13
/T1_G_1: Q2.1, U1.14
/T1_G_2: Q3.1, U1.16
/T1_G_3: Q4.1, U1.19
/T1_G_4: Q5.1, U1.18
/T1_G_5: Q6.1, U1.15
/T1_G_6: Q7.1, U1.3
/T1_G_7: Q8.1, U1.4
/T1_G_8: Q9.1, U1.17
/T1_G_9: Q10.1, U1.12
/T2_C_0: Q11.3, T2.1
/T2_C_1: Q12.3, T2.2
/T2_C_2: Q13.3, T2.3
/T2_C_3: Q14.3, T2.4
/T2_C_4: Q15.3, T2.5
/T2_C_5: Q16.3, T2.6
/T2_C_6: Q17.3, T2.7
/T2_C_7: Q18.3, T2.8
/T2_C_8: Q19.3, T2.9
/T2_C_9: Q20.3, T2.10
/T2_E_0: Q11.2, R11.1
/T2_E_1: Q12.2, R12.1
/T2_E_2: Q13.2, R13.1
/T2_E_3: Q14.2, R14.1
/T2_E_4: Q15.2, R15.1
/T2_E_5: Q16.2, R16.1
/T2_E_6: Q17.2, R17.1
/T2_E_7: Q18.2, R18.1
/T2_E_8: Q19.2, R19.1
/T2_E_9: Q20.2, R20.1
/T2_G_0: Q11.1, U1.9
/T2_G_1: Q12.1, U1.10
/T2_G_2: Q13.1, U1.5
/T2_G_3: Q14.1, U2.7
/T2_G_4: Q15.1, U2.4
/T2_G_5: Q16.1, U1.7
/T2_G_6: Q17.1, U2.5
/T2_G_7: Q18.1, U2.6
/T2_G_8: Q19.1, U1.6
/T2_G_9: Q20.1, U1.8
/T3_C_0: Q21.3, T3.1
/T3_C_1: Q22.3, T3.2
/T3_C_2: Q23.3, T3.3
/T3_C_3: Q24.3, T3.4
/T3_C_4: Q25.3, T3.5
/T3_C_5: Q26.3, T3.6
/T3_C_6: Q27.3, T3.7
/T3_C_7: Q28.3, T3.8
/T3_C_8: Q29.3, T3.9
/T3_C_9: Q30.3, T3.10
/T3_E_0: Q21.2, R21.1
/T3_E_1: Q22.2, R22.1
/T3_E_2: Q23.2, R23.1
/T3_E_3: Q24.2, R24.1
/T3_E_4: Q25.2, R25.1
/T3_E_5: Q26.2, R26.1
/T3_E_6: Q27.2, R27.1
/T3_E_7: Q28.2, R28.1
/T3_E_8: Q29.2, R29.1
/T3_E_9: Q30.2, R30.1
/T3_G_0: Q21.1, U3.13
/T3_G_1: Q22.1, U3.14
/T3_G_2: Q23.1, U3.16
/T3_G_3: Q24.1, U2.16
/T3_G_4: Q25.1, U2.17
/T3_G_5: Q26.1, U3.15
/T3_G_6: Q27.1, U2.18
/T3_G_7: Q28.1, U2.15
/T3_G_8: Q29.1, U3.17
/T3_G_9: Q30.1, U3.12
/T4_C_0: Q31.3, T4.1
/T4_C_1: Q32.3, T4.2
/T4_C_2: Q33.3, T4.3
/T4_C_3: Q34.3, T4.4
/T4_C_4: Q35.3, T4.5
/T4_C_5: Q36.3, T4.6
/T4_C_6: Q37.3, T4.7
/T4_C_7: Q38.3, T4.8
/T4_C_8: Q39.3, T4.9
/T4_C_9: Q40.3, T4.10
/T4_E_0: Q31.2, R31.1
/T4_E_1: Q32.2, R32.1
/T4_E_2: Q33.2, R33.1
/T4_E_3: Q34.2, R34.1
/T4_E_4: Q35.2, R35.1
/T4_E_5: Q36.2, R36.1
/T4_E_6: Q37.2, R37.1
/T4_E_7: Q38.2, R38.1
/T4_E_8: Q39.2, R39.1
/T4_E_9: Q40.2, R40.1
/T4_G_0: Q31.1, U3.9
/T4_G_1: Q32.1, U3.10
/T4_G_2: Q33.1, U3.5
/T4_G_3: Q34.1, U3.18
/T4_G_4: Q35.1, U3.19
/T4_G_5: Q36.1, U3.7
/T4_G_6: Q37.1, U3.4
/T4_G_7: Q38.1, U3.3
/T4_G_8: Q39.1, U3.6
/T4_G_9: Q40.1, U3.8
/VDD: C1.1, C2.1, C3.1, J1.1, U1.25, U1.26, U2.25, U2.27, U3.25, U3.26, U3.27
/nOE: J1.5, U1.20, U2.20, U3.20
unnamed: Q41.1, U2.19
unnamed: Q41.2, R41.1
unnamed: Q41.3, T5.2

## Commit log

2020-06-26 Publish
2020-06-26 remove extra folder
2022-05-09 Clean up for readability
2022-05-09 Final Image
